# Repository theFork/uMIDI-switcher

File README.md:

# uMIDI switcher
Effect switching module based on uMIDI.

* 5 true-bypass loopers
* 2 general purpose switches
* Tuner output
* 3 9V outputs connected to 6 barrel jacks
* 12V input via barrel jack

## Control panel
There are nine illuminated momentary switches on the control panel:

* 1x Mute/Tune (red)
* 5x Looper (green)
* 2x Switch (blue, small)
* 1x Save (red, small)

Except for the "Save" button, the switch LED is synchronously switched with the corresponding relais. It is possible to hard-wire these LEDs to the switch PCB's inputs. The "Save" button should blink to indicate unsaved changes.

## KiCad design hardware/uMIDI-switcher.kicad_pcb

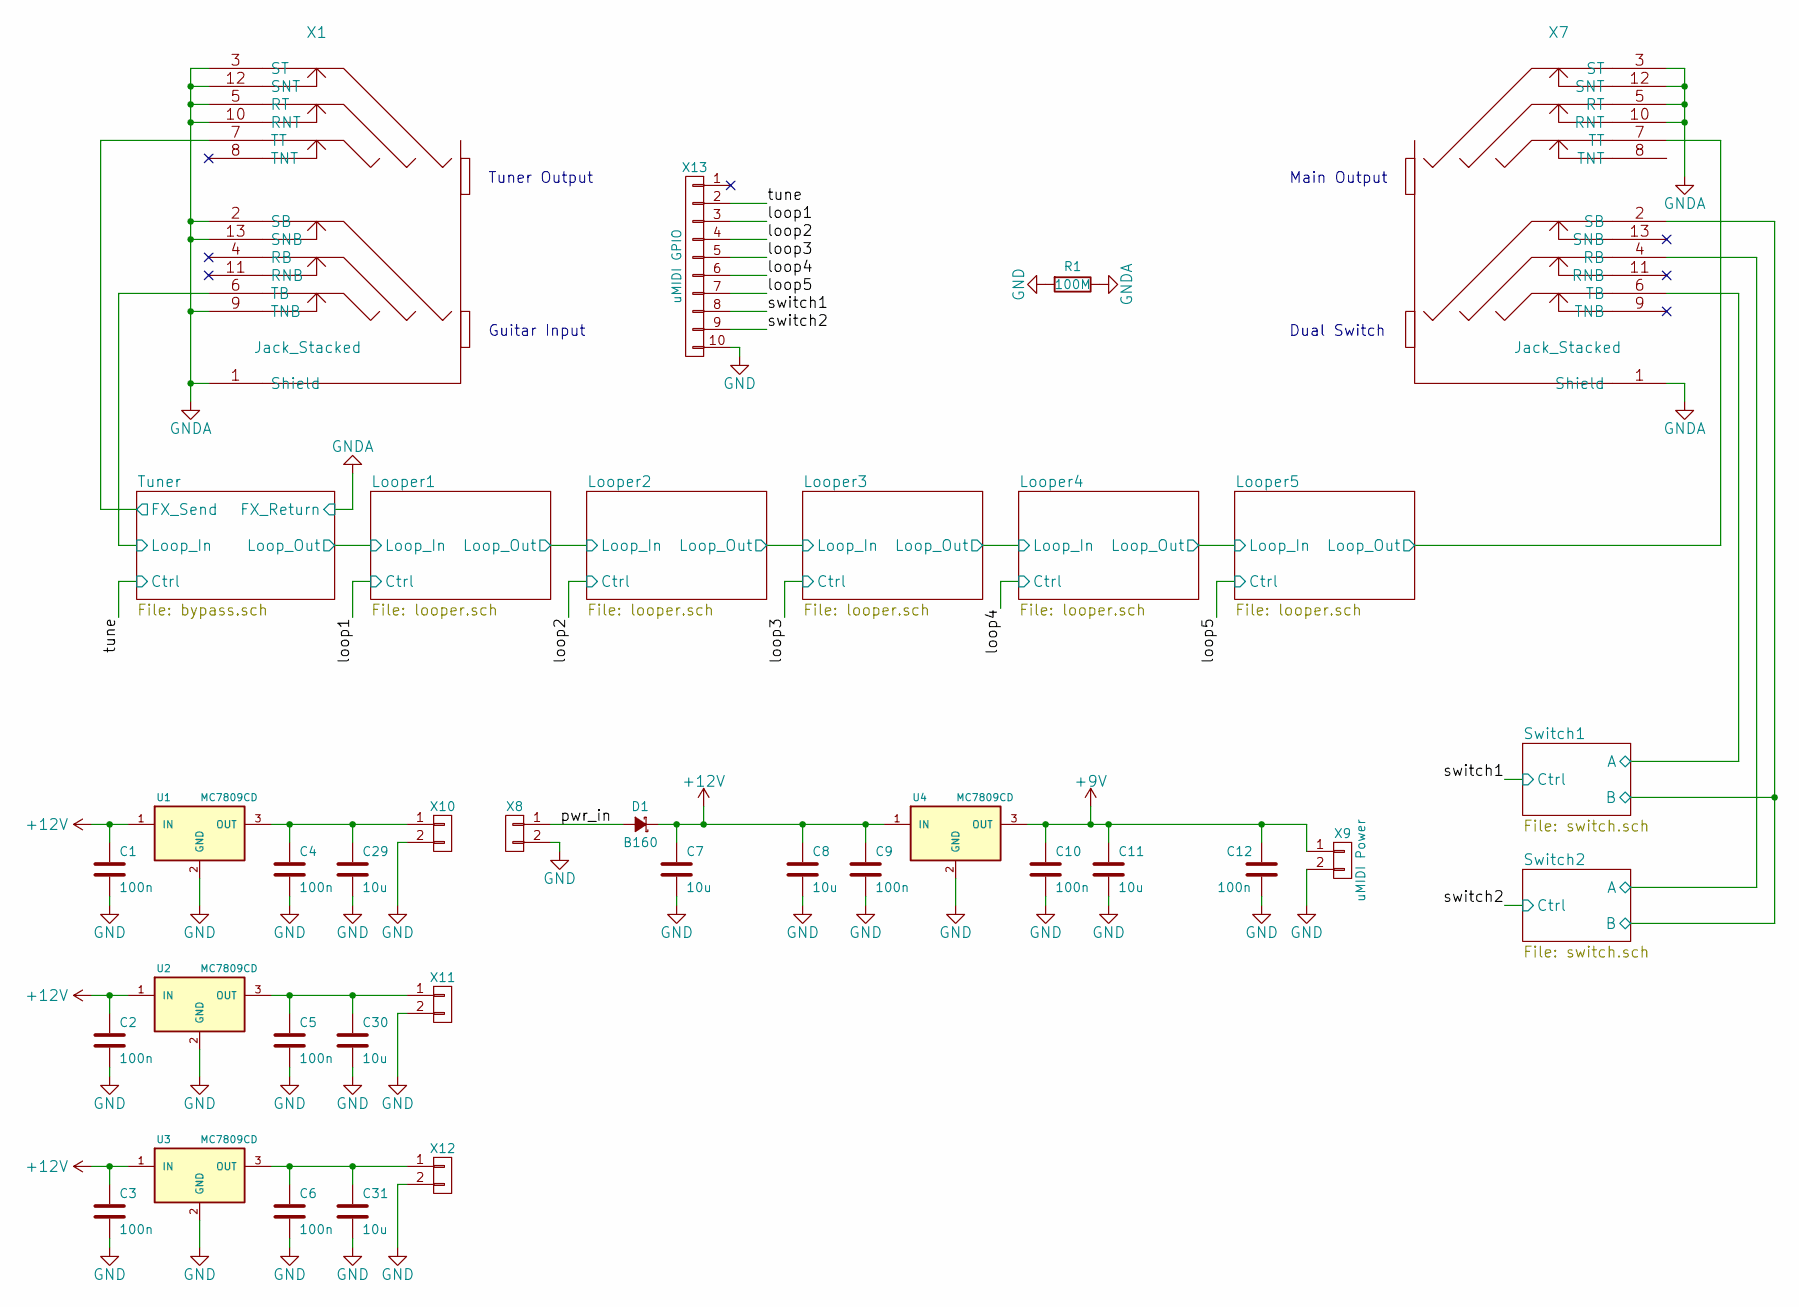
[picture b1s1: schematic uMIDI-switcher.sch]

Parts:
C1, C2, C3, C4, C5, C6, C9, C10, C12: 100n; C_0603; Manufacturer Part Number GRM188R71E104KA01D
C7, C8, C11, C29, C30, C31: 10u; C_0805; Manufacturer Part Number GRM21BR61E106KA73L
D1: B160; SMA_Standard; Manufacturer Part Number B160-13-F
R1: 100M; R_0603; Manufacturer Part Number CRCW0603100MJPEAHR
U1, U2, U3, U4: MC7809CD; D2PAK-3; Manufacturer Part Number MC7809CD2TG
X1, X7: Jack_Stacked; NSJ12HF-1; Manufacturer Part Number NSJ12HF-1
X8: 12V in; PINHEAD-Supply
X9: uMIDI Power; PINHEAD-Supply
X10, X11, X12: CONN_01X02; PINHEAD-Supply
X13: uMIDI GPIO; VASCH5x2; Manufacturer Part Number 30310-6002HB

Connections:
+9V: C10.1, C11.1, C12.1, U4.3 (OUT), X9.1; also elsewhere on the board
+12V: C1.1, C2.1, C3.1, C7.1, C8.1, C9.1, D1.1 (K), U1.1 (IN), U2.1 (IN), U3.1 (IN), U4.1 (IN)
/Looper1/Ctrl: X13.3; also elsewhere on the board
/Looper2/Ctrl: X13.4; also elsewhere on the board
/Looper3/Ctrl: X13.5; also elsewhere on the board
/Looper4/Ctrl: X13.6; also elsewhere on the board
/Looper5/Ctrl: X13.7; also elsewhere on the board
/Looper5/Loop_Out: X7.7 (TT); also elsewhere on the board
/Switch1/A: X7.6 (TB); also elsewhere on the board
/Switch1/B: X7.2 (SB); also elsewhere on the board
/Switch1/Ctrl: X13.8; also elsewhere on the board
/Switch2/A: X7.4 (RB); also elsewhere on the board
/Switch2/Ctrl: X13.9; also elsewhere on the board
/Tuner/Ctrl: X13.2; also elsewhere on the board
/Tuner/FX_Send: X1.7 (TT); also elsewhere on the board
/Tuner/Loop_In: X1.6 (TB); also elsewhere on the board
/pwr_in: D1.2 (A), X8.1
GND: C1.2, C2.2, C3.2, C4.2, C5.2, C6.2, C7.2, C8.2, C9.2, C10.2, C11.2, C12.2, C29.2, C30.2, C31.2, R1.2, U1.2 (GND), U2.2 (GND), U3.2 (GND), U4.2 (GND), X8.2, X9.2, X10.2, X11.2, X12.2, X13.10; also elsewhere on the board
unnamed: C4.1, C29.1, U1.3 (OUT), X10.1
unnamed: C5.1, C30.1, U2.3 (OUT), X11.1
unnamed: C6.1, C31.1, U3.3 (OUT), X12.1

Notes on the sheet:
Guitar Input
Tuner Output
Main Output
Dual Switch

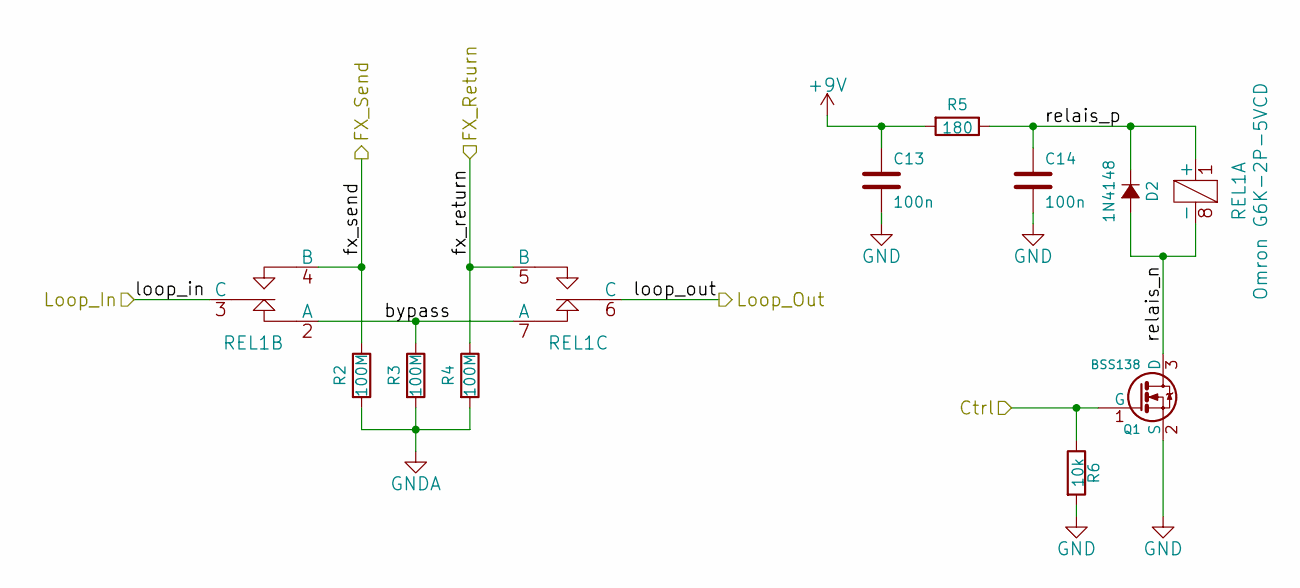
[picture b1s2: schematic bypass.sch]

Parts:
C13, C14: 100n; C_0603; Manufacturer Part Number GRM188R71E104KA01D
D2: 1N4148; SOD-123; Manufacturer Part Number 1N4148W-7-F
Q1: BSS138; SOT-23; Manufacturer Part Number BSS138
R2, R3, R4: 100M; R_0603; Manufacturer Part Number CRCW0603100MJPEAHR
R5: 180; R_0603; Manufacturer Part Number CRCW0603180RJNEA
R6: 10k; R_0603; Manufacturer Part Number CRCW060310K0JNEA
REL1: Omron G6K-2P-5VCD; Omron_G6K-2P; Manufacturer Part Number G6K-2P-Y-DC5

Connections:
+9V: C13.1, R5.2; also elsewhere on the board
/Looper1/Loop_In: REL1.6 (C); also elsewhere on the board
/Tuner/Ctrl: Q1.1 (G), R6.1; also elsewhere on the board
/Tuner/FX_Send: R2.1, REL1.4 (B); also elsewhere on the board
/Tuner/Loop_In: REL1.3 (C); also elsewhere on the board
/Tuner/bypass: R3.1, REL1.2 (A), REL1.7 (A)
/Tuner/relais_n: D2.2 (A), Q1.3 (D), REL1.8 (-)
/Tuner/relais_p: C14.1, D2.1 (K), R5.1, REL1.1 (+)
GND: C13.2, C14.2, Q1.2 (S), R6.2; also elsewhere on the board

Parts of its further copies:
C15, C16, C17, C18, C19, C20, C21, C22, C23, C24: 100n; C_0603; Manufacturer Part Number GRM188R71E104KA01D
D3, D4, D5, D6, D7: 1N4148; SOD-123; Manufacturer Part Number 1N4148W-7-F
Q2, Q3, Q4, Q5, Q6: BSS138; SOT-23; Manufacturer Part Number BSS138
R7, R8, R9, R12, R13, R14, R17, R18, R19, R22, R23, R24, R27, R28, R29: 100M; R_0603; Manufacturer Part Number CRCW0603100MJPEAHR
R10, R15, R20, R25, R30: 180; R_0603; Manufacturer Part Number CRCW0603180RJNEA
R11, R16, R21, R26, R31: 10k; R_0603; Manufacturer Part Number CRCW060310K0JNEA
REL2, REL3, REL4, REL5, REL6: Omron G6K-2P-5VCD; Omron_G6K-2P; Manufacturer Part Number G6K-2P-Y-DC5

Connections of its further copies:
+9V: C15.1, C17.1, C19.1, C21.1, C23.1, R10.2, R15.2, R20.2, R25.2, R30.2; also elsewhere on the board
/Looper1/Ctrl: Q6.1 (G), R31.1; also elsewhere on the board
/Looper1/Loop_In: REL2.3 (C); also elsewhere on the board
/Looper1/Single True Bypass/FX_Return: R29.1, REL2.5 (B); also elsewhere on the board
/Looper1/Single True Bypass/FX_Send: R27.1, REL2.4 (B); also elsewhere on the board
/Looper1/Single True Bypass/bypass: R28.1, REL2.2 (A), REL2.7 (A)
/Looper1/Single True Bypass/relais_n: D7.2 (A), Q6.3 (D), REL2.8 (-)
/Looper1/Single True Bypass/relais_p: C24.1, D7.1 (K), R30.1, REL2.1 (+)
/Looper2/Ctrl: Q2.1 (G), R11.1; also elsewhere on the board
/Looper2/Loop_In: REL2.6 (C), REL3.3 (C)
/Looper2/Single True Bypass/FX_Send: R7.1, REL3.4 (B); also elsewhere on the board
/Looper2/Single True Bypass/bypass: R8.1, REL3.2 (A), REL3.7 (A)
/Looper2/Single True Bypass/relais_n: D3.2 (A), Q2.3 (D), REL3.8 (-)
/Looper2/Single True Bypass/relais_p: C16.1, D3.1 (K), R10.1, REL3.1 (+)
/Looper3/Ctrl: Q3.1 (G), R16.1; also elsewhere on the board
/Looper3/Loop_In: REL3.6 (C), REL4.3 (C)
/Looper3/Single True Bypass/FX_Return: R14.1, REL4.5 (B); also elsewhere on the board
/Looper3/Single True Bypass/FX_Send: R12.1, REL4.4 (B); also elsewhere on the board
/Looper3/Single True Bypass/bypass: R13.1, REL4.2 (A), REL4.7 (A)
/Looper3/Single True Bypass/relais_n: D4.2 (A), Q3.3 (D), REL4.8 (-)
/Looper3/Single True Bypass/relais_p: C18.1, D4.1 (K), R15.1, REL4.1 (+)
/Looper4/Ctrl: Q4.1 (G), R21.1; also elsewhere on the board
/Looper4/Loop_In: REL4.6 (C), REL5.3 (C)
/Looper4/Single True Bypass/FX_Return: R19.1, REL5.5 (B); also elsewhere on the board
/Looper4/Single True Bypass/FX_Send: R17.1, REL5.4 (B); also elsewhere on the board
/Looper4/Single True Bypass/bypass: R18.1, REL5.2 (A), REL5.7 (A)
/Looper4/Single True Bypass/relais_n: D5.2 (A), Q4.3 (D), REL5.8 (-)
/Looper4/Single True Bypass/relais_p: C20.1, D5.1 (K), R20.1, REL5.1 (+)
/Looper5/Ctrl: Q5.1 (G), R26.1; also elsewhere on the board
/Looper5/Loop_In: REL5.6 (C), REL6.3 (C)
/Looper5/Loop_Out: REL6.6 (C); also elsewhere on the board
/Looper5/Single True Bypass/FX_Return: R24.1, REL6.5 (B); also elsewhere on the board
/Looper5/Single True Bypass/FX_Send: R22.1, REL6.4 (B); also elsewhere on the board
/Looper5/Single True Bypass/bypass: R23.1, REL6.2 (A), REL6.7 (A)
/Looper5/Single True Bypass/relais_n: D6.2 (A), Q5.3 (D), REL6.8 (-)
/Looper5/Single True Bypass/relais_p: C22.1, D6.1 (K), R25.1, REL6.1 (+)
GND: C15.2, C16.2, C17.2, C18.2, C19.2, C20.2, C21.2, C22.2, C23.2, C24.2, Q2.2 (S), Q3.2 (S), Q4.2 (S), Q5.2 (S), Q6.2 (S), R11.2, R16.2, R21.2, R26.2, R31.2; also elsewhere on the board

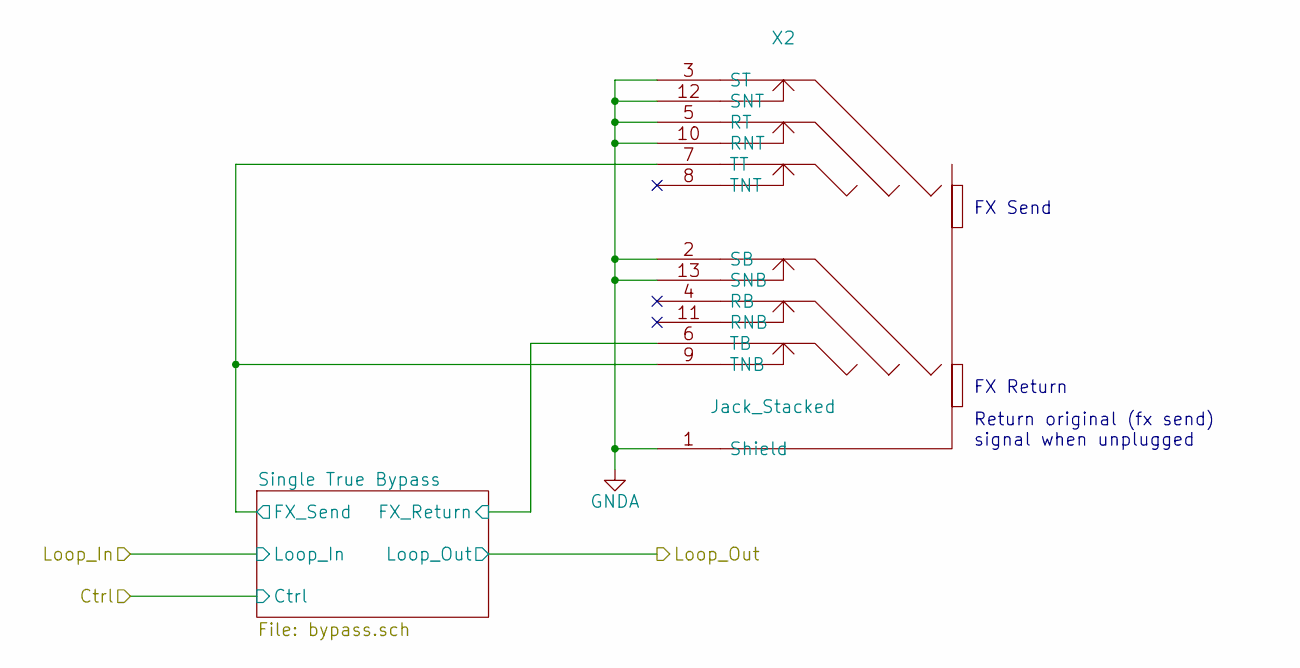
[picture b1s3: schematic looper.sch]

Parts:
X3: Jack_Stacked; NSJ12HF-1; Manufacturer Part Number NSJ12HF-1

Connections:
/Looper2/Single True Bypass/FX_Send: X3.7 (TT), X3.9 (TNB); also elsewhere on the board

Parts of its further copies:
X2, X4, X5, X6: Jack_Stacked; NSJ12HF-1; Manufacturer Part Number NSJ12HF-1

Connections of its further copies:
/Looper1/Single True Bypass/FX_Return: X2.6 (TB); also elsewhere on the board
/Looper1/Single True Bypass/FX_Send: X2.7 (TT), X2.9 (TNB); also elsewhere on the board
/Looper3/Single True Bypass/FX_Return: X4.6 (TB); also elsewhere on the board
/Looper3/Single True Bypass/FX_Send: X4.7 (TT), X4.9 (TNB); also elsewhere on the board
/Looper4/Single True Bypass/FX_Return: X5.6 (TB); also elsewhere on the board
/Looper4/Single True Bypass/FX_Send: X5.7 (TT), X5.9 (TNB); also elsewhere on the board
/Looper5/Single True Bypass/FX_Return: X6.6 (TB); also elsewhere on the board
/Looper5/Single True Bypass/FX_Send: X6.7 (TT), X6.9 (TNB); also elsewhere on the board

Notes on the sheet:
FX Send
FX Return
Return original (fx send) signal when unplugged

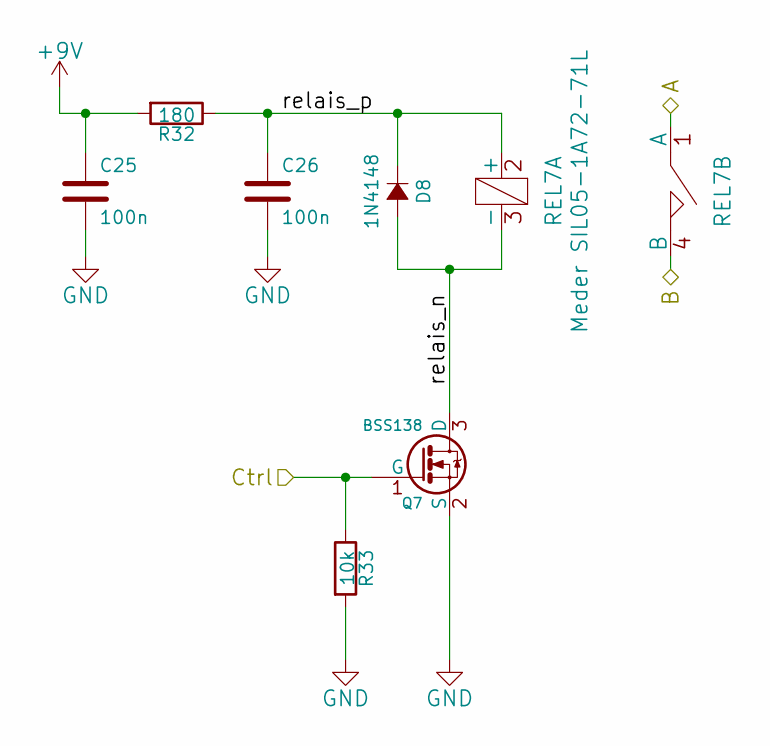
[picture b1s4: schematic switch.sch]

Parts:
C25, C26: 100n; C_0603; Manufacturer Part Number GRM188R71E104KA01D
D8: 1N4148; SOD-123; Manufacturer Part Number 1N4148W-7-F
Q7: BSS138; SOT-23; Manufacturer Part Number BSS138
R32: 180; R_0603; Manufacturer Part Number CRCW0603180RJNEA
R33: 10k; R_0603; Manufacturer Part Number CRCW060310K0JNEA
REL7: Meder SIL05-1A72-71L; Meder_SIL; Part Number SIL 7271-L 5V

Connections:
+9V: C25.1, R32.2; also elsewhere on the board
/Switch1/A: REL7.1 (A); also elsewhere on the board
/Switch1/B: REL7.4 (B); also elsewhere on the board
/Switch1/Ctrl: Q7.1 (G), R33.1; also elsewhere on the board
/Switch1/relais_n: D8.2 (A), Q7.3 (D), REL7.3 (-)
/Switch1/relais_p: C26.1, D8.1 (K), R32.1, REL7.2 (+)
GND: C25.2, C26.2, Q7.2 (S), R33.2; also elsewhere on the board

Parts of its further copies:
C27, C28: 100n; C_0603; Manufacturer Part Number GRM188R71E104KA01D
D9: 1N4148; SOD-123; Manufacturer Part Number 1N4148W-7-F
Q8: BSS138; SOT-23; Manufacturer Part Number BSS138
R34: 180; R_0603; Manufacturer Part Number CRCW0603180RJNEA
R35: 10k; R_0603; Manufacturer Part Number CRCW060310K0JNEA
REL8: Meder SIL05-1A72-71L; Meder_SIL; Part Number SIL 7271-L 5V

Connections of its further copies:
+9V: C27.1, R34.2; also elsewhere on the board
/Switch1/B: REL8.4 (B); also elsewhere on the board
/Switch2/A: REL8.1 (A); also elsewhere on the board
/Switch2/Ctrl: Q8.1 (G), R35.1; also elsewhere on the board
/Switch2/relais_n: D9.2 (A), Q8.3 (D), REL8.3 (-)
/Switch2/relais_p: C28.1, D9.1 (K), R34.1, REL8.2 (+)
GND: C27.2, C28.2, Q8.2 (S), R35.2; also elsewhere on the board

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
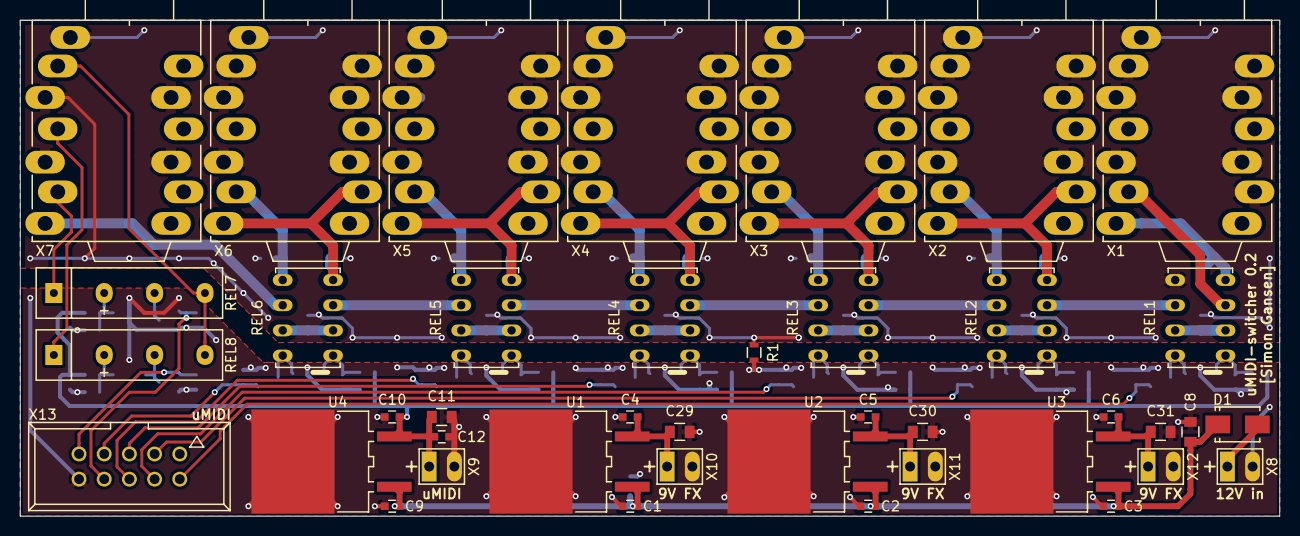
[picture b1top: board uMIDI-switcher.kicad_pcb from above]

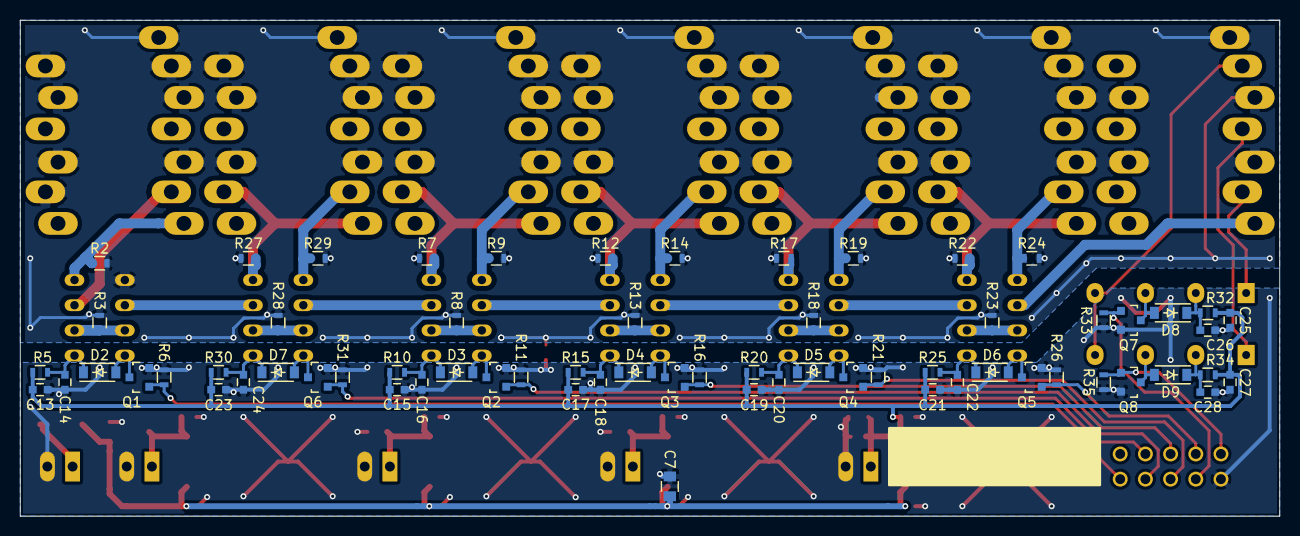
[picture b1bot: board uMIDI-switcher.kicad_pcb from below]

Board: 2 copper layers, 127.0 x 50.0 mm, 107 parts (66 on the bottom side), 59 nets.

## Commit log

2015-10-16 Remove led distribution
2015-10-16 Use smd regulators
2015-10-16 Use schottky diode for input protection
2015-10-16 Integrate sheet looper.sch into top level sheet
2015-10-16 Add optional gnd-gnda resistor
2015-10-19 Annotate
2015-10-19 Change D1 supplier
2015-10-19 Unify part fields
2015-10-19 Re-Annotate
2015-10-19 Change LDO supplier
2015-10-23 Add some component fields; Change 10uF footprint
2015-10-24 Determine relay resistor
2015-10-24 Remove datasheets. These are now linked.
2015-11-19 Fix ribbon connector supplier fields
2015-11-20 Straighten annotation and placement
2015-11-20 Remove tuner signal to GNDA resistor (only on board)
2015-11-20 Assign net classes
2015-11-20 Use two layers; Shrink placement
2015-11-20 Route everything except GND(A)
2015-11-20 Add GND and GNDA planes
2015-11-26 Revise omron relais footprint (silk only)
2015-11-26 Add fitting footprint for voltage regulators
2015-11-26 Use new ldo footprint; Adapt placement
2015-11-26 Place and route
2015-11-26 Add 10uF caps to 9V outputs; Place and route
2015-11-27 Finish routing
2015-11-27 Revise pcb (and some footprints) silk screen
2015-11-29 Revise bottom silk screen; DRC clean
2015-11-30 Fix major footprint fuckups...
2015-11-30 Revise silkscreen
2015-11-30 Add gerber archive
2015-12-18 Fix faulty jack connections
2015-12-18 Fix some silkscreen designators
2015-12-18 Increase size of polarity markers
2015-12-18 Add comment area to bottom silk
2015-12-18 Update gerber files
2016-01-05 Add backside drill plan
2016-02-05 Add control panel concept and drawing
2016-02-06 Revise control panel drawing
